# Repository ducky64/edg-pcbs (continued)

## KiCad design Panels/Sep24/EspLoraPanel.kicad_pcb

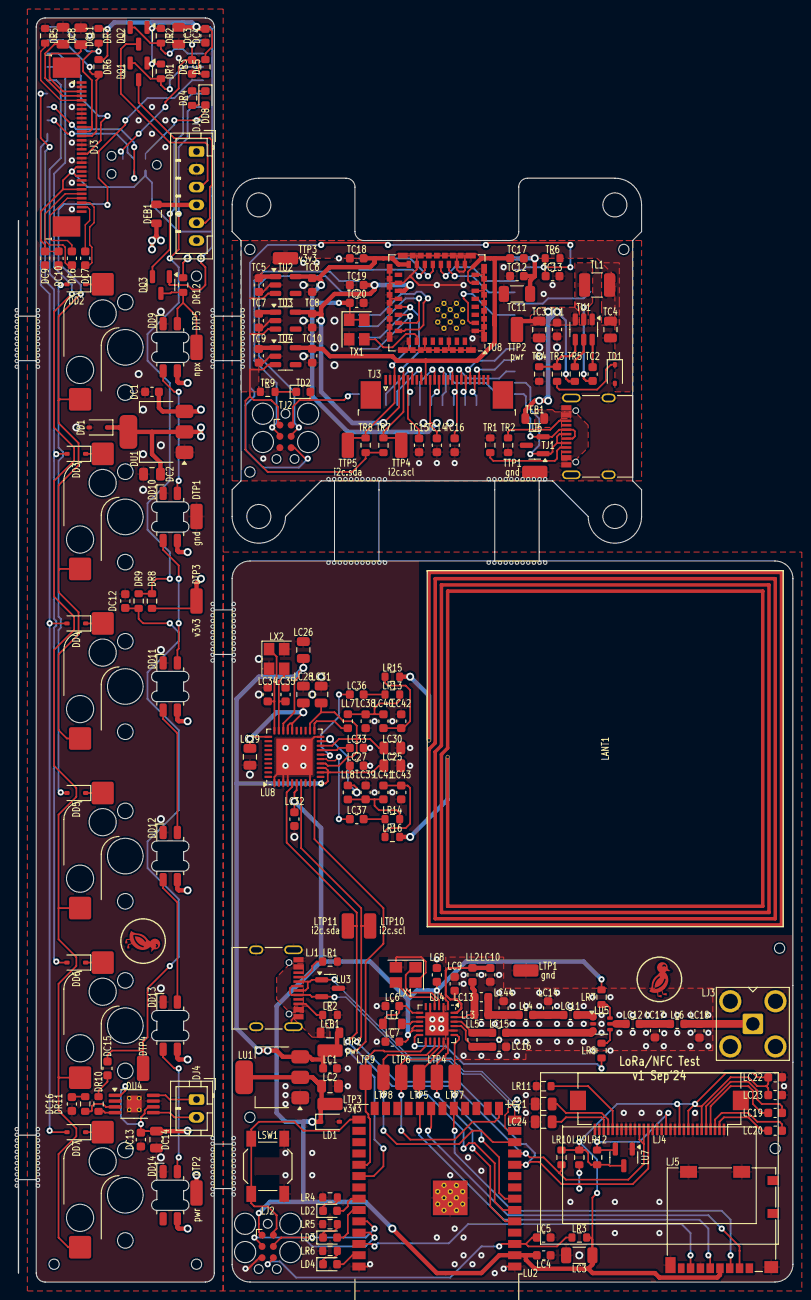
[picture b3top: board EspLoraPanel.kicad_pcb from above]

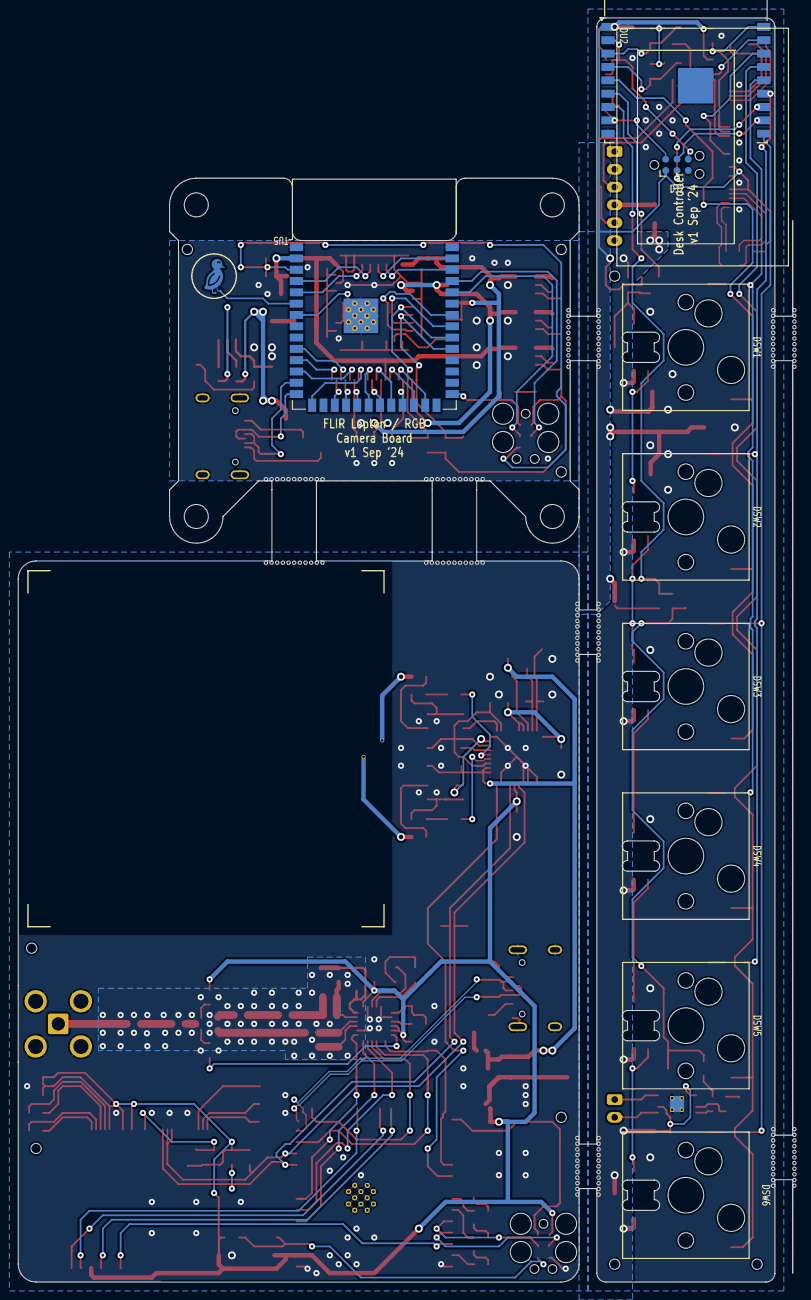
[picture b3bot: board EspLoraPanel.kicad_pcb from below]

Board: 2 copper layers, 87.0 x 142.0 mm, 227 parts (20 on the bottom side), 167 nets.

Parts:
DC1, DC4, DC13: 50V 100nF X7R ±10% 0603 Multilayer Ceramic Capaci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; C_0603_1608Metric
DC2, DC8: 25V 4.7uF X5R ±10% 0805 Multilayer Ceramic Capaci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; C_0805_2012Metric
DC3, DC11, DC14: 25V 10uF X5R ±10% 0805 Multilayer Ceramic Capacit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; C_0805_2012Metric
DC5, DC6, DC7, DC9, DC10, DC15, DC16: 50V 1uF X5R ±10% 0603 Multilayer Ceramic Capacito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; C_0603_1608Metric
DC12: 50V 33nF X7R ±10% 0603 Multilayer Ceramic Capacit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; C_0603_1608Metric
DD1: 3.6V~3.8V 200mW 3.6V SOD-323 Zener Diodes ROHS; D_SOD-323
DD2, DD3, DD4, DD5, DD6, DD7: 40V 600mV@1A 1A SOD-323 Schottky Diodes ROHS; D_SOD-323
DD8: -40?~+85? Red 0603 LED Indication - Discrete ROHS; LED_0603_1608Metric
DD9, DD10, DD11, DD12, DD13, DD14: SK6812MINI-E; LED_SK6812MINI-E
DFB1: ±25% 100?@100MHz 0805 Ferrite Beads ROHS; L_0805_2012Metric
DH1, DH2, DH3: JlcToolingHole_1.152mm
DJ1: B6B-PH-K; JST_PH_B6B-PH-K_1x06_P2.00mm_Vertical
DJ2: Tag-Connect_TC2030-IDC-NL_2x03_P1.27mm_Vertical
DJ3: AFC07-S30ECA-00; TE_3-1734839-0_1x30-1MP_P0.5mm_Horizontal
DJ4: B2B-PH-K; JST_PH_B2B-PH-K_1x02_P2.00mm_Vertical
DQ1, DQ2, DQ3: 30V 5.7A 26.5m?@10V,5.7A 1.4W 1.5V@250uA 1PCSNCha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; SOT-23
DR1, DR2, DR6, DR7, DR8, DR12: 100mW Thick Film Resistors 75V ±100ppm/? ±1% 4.7k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; R_0603_1608Metric
DR3: 100mW Thick Film Resistors 75V ±100ppm/? ±1% 10k?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; R_0603_1608Metric
DR4: 100mW Thick Film Resistors 75V ±100ppm/? ±1% 820?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; R_0603_1608Metric
DR5: 100mW Thick Film Resistors 75V ±100ppm/? ±1% 470k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; R_0603_1608Metric
DR9: 100mW Thick Film Resistors 75V ±100ppm/? ±1% 1k? 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; R_0603_1608Metric
DR10, DR11: 100mW Thick Film Resistors 75V ±100ppm/? ±1% 68k?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; R_0603_1608Metric
DSW1, DSW2, DSW3, DSW4, DSW5, DSW6: PG151101S11; SW_Hotswap_Kailh_MX
DTP1: gnd; TestPoint_TE_RCT_0805
DTP2: pwr; TestPoint_TE_RCT_0805
DTP3: v3v3; TestPoint_TE_RCT_0805
DTP4: spk_chain_1; TestPoint_TE_RCT_0805
DTP5: npx; TestPoint_TE_RCT_0805
DU1: LDL1117S33R; SOT-223-3_TabPin2
DU2: ESP32-C3-WROOM-02; ESP-WROOM-02
DU3: ER-OLED-0.96-1.1; Lcd_Er_Oled0.96_1.1_Outline
DU4: TPA2005D1; MSOP-8-1EP_3x3mm_P0.65mm_EP1.68x1.88mm_ThermalVias
LANT1: an13219
LC1, LC4, LC7, LC27, LC33: 50V 100nF X7R ±10% 0603 Multilayer Ceramic Capaci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; C_0603_1608Metric
LC2, LC21, LC25, LC26: 25V 4.7uF X5R ±10% 0805 Multilayer Ceramic Capaci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; C_0805_2012Metric
LC3: 25V 22uF X5R ±10% 1206 Multilayer Ceramic Capacit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; C_1206_3216Metric
LC5, LC8, LC19, LC20, LC22, LC23, LC32: 50V 1uF X5R ±10% 0603 Multilayer Ceramic Capacito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; C_0603_1608Metric
LC6: 25V 470nF X7R ±10% 0603 Multilayer Ceramic Capaci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; C_0603_1608Metric
LC9, LC11, LC12, LC42, LC43: 50V 47pF C0G ±5% 0603 Multilayer Ceramic Capacito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; C_0603_1608Metric
LC10: 50V 47nF X7R ±10% 0603 Multilayer Ceramic Capacit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; C_0603_1608Metric
LC13: 250V 2.2pF NP0 ±5% 0603 Multilayer Ceramic Capaci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; C_0603_1608Metric
LC14, LC15, LC16, LC17, LC18: 250V 3pF C0G ±5% 0603 Multilayer Ceramic Capacito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; C_0603_1608Metric
LC24: 25V 10uF X5R ±10% 0805 Multilayer Ceramic Capacit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; C_0805_2012Metric
LC28, LC29, LC30, LC31: 50V 2.2uF X5R ±10% 0805 Multilayer Ceramic Capaci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; C_0805_2012Metric
LC34, LC35, LC44: 50V 10pF C0G ±5% 0603 Multilayer Ceramic Capacito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; C_0603_1608Metric
LC36, LC37: 50V 1nF X7R ±10% 0603 Multilayer Ceramic Capacito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; C_0603_1608Metric
LC38, LC39: 50V 560pF X7R ±10% 0603 Multilayer Ceramic Capaci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; C_0603_1608Metric
LC40, LC41: 50V 150pF X7R ±10% 0603 Multilayer Ceramic Capaci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; C_0603_1608Metric
LD1: 3.6V~3.8V 200mW 3.6V SOD-323 Zener Diodes ROHS; D_SOD-323
LD2: -40?~+85? Red 0603 LED Indication - Discrete ROHS; LED_0603_1608Metric
LD3: 20mA Colorless transparent lens -40?~+85? 585.5nm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; LED_0603_1608Metric
LD4: White 0603 LED Indication - Discrete ROHS; LED_0603_1608Metric
LFB1: ±25% 100?@100MHz 0805 Ferrite Beads ROHS; L_0805_2012Metric
LH1, LH2, LH3: JlcToolingHole_1.152mm
LJ1: COM-15111; USB_C_Receptacle_XKB_U262-16XN-4BVC11
LJ2: Tag-Connect_TC2030-IDC-FP_2x03_P1.27mm_Vertical
LJ3: 901-143; SMA_Amphenol_901-143_Horizontal
LJ4: AFC01-S30FCA-00; Hirose_FH12-30S-0.5SH_1x30-1MP_P0.50mm_Horizontal
LJ5: 104031-0811; microSD_HC_Molex_104031-0811
LL1: 100mA 15uH ±20% 650m? 0805 Inductors (SMD) ROHS; L_0805_2012Metric
LL2: 200mA 47nH ±5% 1? 0603 Inductors (SMD) ROHS; L_0603_1608Metric
LL3: 700mA 3.3nH ±5% 0603 Power Inductors ROHS; L_0603_1608Metric
LL4, LL6: 500mA 8.2nH ±5% 350m? 0603 Inductors (SMD) ROHS; L_0603_1608Metric
LL5: 300mA 12nH ±5% 450m? 0603 Inductors (SMD) ROHS; L_0603_1608Metric
LL7, LL8: 900mA 220nH ±5% 200m? 0603 Inductors (SMD) ROHS; L_0603_1608Metric
LR1, LR2: 100mW Thick Film Resistors 75V ±100ppm/? ±1% 5.1k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; R_0603_1608Metric
LR3, LR12: 100mW Thick Film Resistors 75V ±100ppm/? ±1% 10k?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; R_0603_1608Metric
LR4, LR5, LR6: 100mW Thick Film Resistors 75V ±100ppm/? ±1% 820?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; R_0603_1608Metric
LR7, LR8: 100mW Thick Film Resistors 75V ±100ppm/? ±1% 1k? 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; R_0603_1608Metric
LR9, LR10: 100mW Thick Film Resistors 75V ±100ppm/? ±1% 4.7k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; R_0603_1608Metric
LR11: 100mW Thick Film Resistors 75V ±100ppm/? ±1% 470k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; R_0603_1608Metric
LR13, LR14: 100mW Thick Film Resistors 75V ±100ppm/? ±1% 2.2k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; R_0603_1608Metric
LR15, LR16: 100mW Thick Film Resistors 75V ±1% ±200ppm/? 2.49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; R_0603_1608Metric
LSW1: 5.1mm switch; SW_SPST_SKQG_WithoutStem
LTP1: gnd; TestPoint_TE_RCT_0805
LTP2: pwr; TestPoint_TE_RCT_0805
LTP3: v3v3; TestPoint_TE_RCT_0805
LTP4: lr.sck; TestPoint_TE_RCT_0805
LTP5: lr.mosi; TestPoint_TE_RCT_0805
LTP6: lr.miso; TestPoint_TE_RCT_0805
LTP7: lr_cs; TestPoint_TE_RCT_0805
LTP8: lr_rs; TestPoint_TE_RCT_0805
LTP9: lr_di; TestPoint_TE_RCT_0805
LTP10: i2c.scl; TestPoint_TE_RCT_0805
LTP11: i2c.sda; TestPoint_TE_RCT_0805
LU1: LDL1117S33R; SOT-223-3_TabPin2
LU2: ESP32-S3-WROOM-1-N16R8; ESP32-S3-WROOM-1
LU3: PESD5V0X1BT; SOT-23
LU4: SX1262IMLTRT; QFN-24-1EP_4x4mm_P0.5mm_EP2.6x2.6mm
LU5: PE4259; SOT-363_SC-70-6
LU6: ER-OLED-0.96-1.1; Lcd_Er_Oled0.96_1.1_Outline
LU7: APX803S-29SA-7; SOT-23
LU8: PN7160A1HN/C100Y; HVQFN-40-1EP_6x6mm_P0.5mm_EP4.1x4.1mm
LX1: 30MHz SMD Crystal Resonator 20pF ±10ppm ±30ppm -4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; Crystal_SMD_3225-4Pin_3.2x2.5mm
LX2: 27.12MHz SMD Crystal Resonator 10pF ±10ppm ±30ppm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; Crystal_SMD_3225-4Pin_3.2x2.5mm
TC1, TC2, TC12, TC14, TC15, TC17, TC18, TC19, TC20: 50V 100nF X7R ±10% 0603 Multilayer Ceramic Capaci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; C_0603_1608Metric
TC3, TC4: 25V 10uF X5R ±10% 0805 Multilayer Ceramic Capacit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; C_0805_2012Metric
TC5, TC6, TC7, TC8, TC9, TC10, TC13: 50V 1uF X5R ±10% 0603 Multilayer Ceramic Capacito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; C_0603_1608Metric
TC11: 25V 22uF X5R ±10% 1206 Multilayer Ceramic Capacit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; C_1206_3216Metric
TC16: 50V 15pF C0G ±5% 0603 Multilayer Ceramic Capacito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; C_0603_1608Metric
TD1: 3.6V~3.8V 200mW 3.6V SOD-323 Zener Diodes ROHS; D_SOD-323
TD2: -40?~+85? Red 0603 LED Indication - Discrete ROHS; LED_0603_1608Metric
TFB1: ±25% 100?@100MHz 0805 Ferrite Beads ROHS; L_0805_2012Metric
TH1, TH2, TH3: JlcToolingHole_1.152mm
TJ1: COM-15111; USB_C_Receptacle_XKB_U262-16XN-4BVC11
TJ2: Tag-Connect_TC2030-IDC-FP_2x03_P1.27mm_Vertical
TJ3: AFC07-S24ECA-00; TE_2-1734839-4_1x24-1MP_P0.5mm_Horizontal
TL1: 1.2A 10uH ±20% 1.6A 305m? 1210 Inductors (SMD) RO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; L_1210_3225Metric
TR1, TR2: 100mW Thick Film Resistors 75V ±100ppm/? ±1% 5.1k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; R_0603_1608Metric
TR3: 100mW Thick Film Resistors 75V ±100ppm/? ±1% 6.8k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; R_0603_1608Metric
TR4: 100mW Thick Film Resistors 75V ±100ppm/? ±1% 1.5k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; R_0603_1608Metric
TR5: 100mW Thick Film Resistors 75V ±100ppm/? ±1% 510k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; R_0603_1608Metric
TR6: 100mW Thick Film Resistors 75V ±100ppm/? ±1% 10k?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; R_0603_1608Metric
TR7, TR8: 100mW Thick Film Resistors 75V ±100ppm/? ±1% 4.7k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; R_0603_1608Metric
TR9: 100mW Thick Film Resistors 75V ±100ppm/? ±1% 820?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; R_0603_1608Metric
TTP1: gnd; TestPoint_TE_RCT_0805
TTP2: pwr; TestPoint_TE_RCT_0805
TTP3: v3v3; TestPoint_TE_RCT_0805
TTP4: i2c.scl; TestPoint_TE_RCT_0805
TTP5: i2c.sda; TestPoint_TE_RCT_0805
TU1: TPS54202H; SOT-23-6
TU2: TLV75730PDBVR; SOT-23-5
TU3: TLV75728PDBVR; SOT-23-5
TU4: TLV75712PDBVR; SOT-23-5
TU5: ESP32-S3-WROOM-1-N16R8; ESP32-S3-WROOM-1
TU6: PESD5V0X1BT; SOT-23
TU7: Symbol_DucklingSolid
TU8: 1050281001; Molex_1050281001
TX1: ±15ppm 1.8V~3.3V 25MHz -40?~+85? SMD-3225_4P Pre-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; Crystal_SMD_3225-4Pin_3.2x2.5mm
svg2mod, svg2mod#2: G***; Symbol_DucklingSolid

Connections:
Dconn.dtx_shift.hv_io: DJ1.5, DQ1.3
Dconn.htx_shift.hv_io: DJ1.3, DQ2.3
Dconn.pwr: DFB1.1, DJ1.4
Dconn.uart.rx: DQ2.2, DR2.2, DU2.3
Dconn.uart.tx: DQ1.2, DR1.2, DU2.4
Dgnd: DC1.2, DC2.2, DC3.2, DC4.2, DC5.2, DC8.2, DC9.2, DC10.2, DC11.2, DC12.2, DC13.2, DC14.2, DC16.2, DD1.2, DD9.3, DD10.3, DD11.3, DD12.3, DD13.3, DD14.3, DJ1.2, DJ2.5, DJ3.1, DJ3.2, DJ3.6, DJ3.7, DJ3.8, DJ3.9, DJ3.10, DJ3.14, DJ3.15, DJ3.16, DJ3.18, DJ3.19, DJ3.21, DJ3.23, DJ3.30, DR4.2, DR5.2, DTP1.1, DU1.1, DU2.9, DU2.19, DU4.7, DU4.9
Di2c_pull.i2c.scl: DJ3.13, DR6.2, DU2.17
Di2c_pull.i2c.sda: DJ3.11, DJ3.12, DR7.2, DU2.18
Dledr.res.a: DD8.1, DR4.1
Dmcu.gpio.swc_0: DSW1.2, DSW2.2, DSW3.2, DU2.5
Dmcu.gpio.swc_1: DSW4.2, DSW5.2, DSW6.2, DU2.15
Dmcu.gpio.swr_0: DD2.2, DD5.2, DU2.14
Dmcu.gpio.swr_1: DD3.2, DD6.2, DU2.13
Dmcu.gpio.swr_2: DD4.2, DD7.2, DU2.10
Dmcu.program_boot_node: DD8.2, DJ2.2, DU2.8
Dmcu.program_en_node: DC5.1, DJ2.6, DR3.2, DU2.2
Dmcu.program_uart_node.a_tx: DJ2.3, DU2.12
Dmcu.program_uart_node.b_tx: DJ2.4, DU2.11
Dnpx.led[0].dout: DD9.2, DD10.4
Dnpx.led[1].dout: DD10.2, DD11.4
Dnpx.led[2].dout: DD11.2, DD12.4
Dnpx.led[3].dout: DD12.2, DD13.4
Dnpx.led[4].dout: DD13.2, DD14.4
Dnpx_shift.hv_io: DD9.4, DQ3.3, DR12.2, DTP5.1
Dnpx_shift.lv_io: DQ3.2, DU2.6
Doled.c1_cap.neg: DC6.2, DJ3.26
Doled.c1_cap.pos: DC6.1, DJ3.27
Doled.c2_cap.neg: DC7.2, DJ3.28
Doled.c2_cap.pos: DC7.1, DJ3.29
Doled.device.vcc: DC11.1, DJ3.3
Doled.device.vcomh: DC8.1, DJ3.4
Doled.iref_res.a: DJ3.5, DR5.1
Doled.reset: DJ3.17, DU2.16
Dpwr: DC1.1, DC13.1, DC14.1, DD9.1, DD10.1, DD11.1, DD12.1, DD13.1, DD14.1, DFB1.2, DR12.1, DTP2.1, DU1.3, DU4.1, DU4.6
Dspk_chain_0: DR8.2, DR9.1, DU2.7
Dspk_chain_1: DC12.1, DC15.2, DR9.2, DTP4.1
Dspk_chain_2.a: DJ4.1, DU4.8
Dspk_chain_2.b: DJ4.2, DU4.5
Dspk_drv.inn_cap.pos: DC16.1, DR11.1
Dspk_drv.inn_res.b: DR11.2, DU4.3
Dspk_drv.inp_cap.pos: DC15.1, DR10.1
Dspk_drv.inp_res.b: DR10.2, DU4.4
Dsw.d[0,0].cathode: DD2.1, DSW1.1
Dsw.d[0,1].cathode: DD3.1, DSW2.1
Dsw.d[0,2].cathode: DD4.1, DSW3.1
Dsw.d[1,0].cathode: DD5.1, DSW4.1
Dsw.d[1,1].cathode: DD6.1, DSW5.1
Dsw.d[1,2].cathode: DD7.1, DSW6.1
Dv3v3: DC2.1, DC3.1, DC4.1, DC9.1, DC10.1, DD1.1, DJ2.1, DJ3.20, DJ3.22, DJ3.25, DQ1.1, DQ2.1, DQ3.1, DR1.1, DR2.1, DR3.1, DR6.1, DR7.1, DR8.1, DTP3.1, DU1.2, DU2.1
Lgnd: LC1.2, LC2.2, LC3.2, LC4.2, LC5.2, LC6.2, LC7.2, LC8.2, LC9.2, LC10.2, LC14.2, LC16.2, LC17.2, LC18.2, LC21.2, LC22.2, LC23.2, LC24.2, LC25.2, LC26.2, LC27.2, LC28.2, LC29.2, LC30.2, LC31.2, LC32.2, LC33.2, LC34.2, LC35.2, LC38.2, LC39.2, LC42.2, LC43.2, LC44.2, LD1.2, LJ1.A1, LJ1.A12, LJ1.B1, LJ1.B12, LJ1.S1, LJ2.5, LJ3.2, LJ4.1, LJ4.8, LJ4.10, LJ4.12, LJ4.13, LJ4.15, LJ4.16, LJ4.17, LJ4.21, LJ4.22, LJ4.23, LJ4.24, LJ4.25, LJ4.29, LJ4.30, LJ5.6, LJ5.11, LR1.1, LR2.1, LR4.2, LR5.2, LR6.2, LR11.2, LSW1.2, LTP1.1, LU1.1, LU2.1, LU2.40, LU2.41, LU3.3, LU4.2, LU4.5, LU4.8, LU4.20, LU4.25, LU5.2, LU7.1, LU8.1, LU8.3, LU8.4, LU8.9, LU8.20, LU8.41, LX1.2, LX1.4, LX2.2, LX2.4
Li2c_pull.i2c.scl: LJ4.18, LR9.2, LTP10.1, LU2.10, LU8.7
Li2c_pull.i2c.sda: LJ4.19, LJ4.20, LR10.2, LTP11.1, LU2.11, LU8.5
Lledb.res.a: LD4.1, LR6.1
Lledb.signal: LD4.2, LU2.39
Lledg.res.a: LD3.1, LR5.1
Lledg.signal: LD3.2, LU2.35
Lledr.res.a: LD2.1, LR4.1
Lledr.signal: LD2.2, LU2.34
Llora.ant_pi.output: LC18.1, LJ3.1, LL6.2
Llora.balun.input: LC15.1, LU5.3
Llora.balun.rfi_n: LC15.2, LL5.1, LU4.22
Llora.balun.rfi_p: LC16.1, LL5.2, LU4.21
Llora.dcc_l.a: LL1.1, LU4.9
Llora.ic.rfo: LC13.2, LL2.2, LL3.1, LU4.23
Llora.ic.vr_pa: LC9.1, LC10.1, LL2.1, LU4.24
Llora.ic.vreg: LC6.1, LL1.2, LU4.7
Llora.rf_sw.ctrl: LR8.1, LU4.12
Llora.rf_sw.ctrl_res.b: LR8.2, LU5.4
Llora.rf_sw.vdd_res.b: LR7.2, LU5.6
Llora.rfc_dcblock.neg: LC12.2, LU5.5
Llora.rfc_dcblock.pos: LC12.1, LC17.1, LL6.1
Llora.tx_dcblock.pos: LC11.1, LU5.1
Llora.tx_pi.output: LC11.2, LC14.1, LL4.2
Llora.xtal.crystal.xtal_in: LU4.3, LX1.1
Llora.xtal.crystal.xtal_out: LU4.4, LX1.3
Lmcu.program_boot_node: LJ2.2, LSW1.1, LU2.27
Lmcu.program_en_node: LC5.1, LJ2.6, LR3.2, LU2.3
Lmcu.program_uart_node.a_tx: LJ2.3, LU2.37
Lmcu.program_uart_node.b_tx: LJ2.4, LU2.36
Lnfc.damp.ant1: LANT1.1, LR15.2
Lnfc.damp.ant2: LANT1.2, LR16.2
Lnfc.emc.out1: LC38.1, LC40.1, LL7.2, LR13.1
Lnfc.emc.out2: LC39.1, LC41.1, LL8.2, LR14.1
Lnfc.ic.rxn: LC37.2, LU8.15
Lnfc.ic.rxp: LC36.2, LU8.16
Lnfc.ic.tx1: LL7.1, LU8.21
Lnfc.ic.tx2: LL8.1, LU8.19
Lnfc.ic.vdd: LC28.1, LC29.1, LU8.26, LU8.27, LU8.31
Lnfc.ic.vddmid: LC33.1, LU8.17
Lnfc.ic.vddtx: LC30.1, LC31.1, LU8.14, LU8.18, LU8.22
Lnfc.ic.xtal.xtal_in: LC34.1, LU8.30, LX2.1
Lnfc.ic.xtal.xtal_out: LC35.1, LU8.29, LX2.3
Lnfc.match.out1: LC40.2, LC42.1, LR15.1
Lnfc.match.out2: LC41.2, LC43.1, LR16.1
Lnfc.reset: LU2.32, LU8.10
Lnfc.rx.rrx1.b: LC36.1, LR13.2
Lnfc.rx.rrx2.b: LC37.1, LR14.2
Loled.c1_cap.neg: LC19.2, LJ4.5
Loled.c1_cap.pos: LC19.1, LJ4.4
Loled.c2_cap.neg: LC20.2, LJ4.3
Loled.c2_cap.pos: LC20.1, LJ4.2
Loled.device.vcc: LC24.1, LJ4.28
Loled.device.vcomh: LC21.1, LJ4.27
Loled.iref_res.a: LJ4.26, LR11.1
Loled_rst.nreset: LJ4.14, LR12.2, LU7.2
Lpwr: LC1.1, LC25.1, LC26.1, LC27.1, LFB1.2, LTP2.1, LU1.3, LU8.12, LU8.13, LU8.28
Lsd.cs: LJ5.2, LU2.21
Lsd.spi.miso: LJ5.7, LU2.38
Lsd.spi.mosi: LJ5.3, LU2.19
Lsd.spi.sck: LJ5.5, LU2.22
Ltp_lora_cs.io: LTP7.1, LU2.7, LU4.19
Ltp_lora_dio.io: LTP9.1, LU2.31, LU4.13
Ltp_lora_rst.io: LTP8.1, LU2.12, LU4.15
Ltp_lora_spi.io.miso: LTP6.1, LU2.15, LU4.16
Ltp_lora_spi.io.mosi: LTP5.1, LU2.6, LU4.17
Ltp_lora_spi.io.sck: LTP4.1, LU2.5, LU4.18
Ltx_cpack.pos.0: LC13.1, LC44.1, LL3.2, LL4.1
Lusb.conn.cc.cc1: LJ1.A5, LR1.2
Lusb.conn.cc.cc2: LJ1.B5, LR2.2
Lusb.pwr: LFB1.1, LJ1.A4, LJ1.A9, LJ1.B4, LJ1.B9
Lusb_chain_0.d_N: LJ1.A7, LJ1.B7, LU2.13, LU3.1
Lusb_chain_0.d_P: LJ1.A6, LJ1.B6, LU2.14, LU3.2
Lv3v3: LC2.1, LC3.1, LC4.1, LC7.1, LC8.1, LC22.1, LC23.1, LC32.1, LD1.1, LJ2.1, LJ4.6, LJ4.9, LJ4.11, LJ5.4, LR3.1, LR7.1, LR9.1, LR10.1, LR12.1, LTP3.1, LU1.2, LU2.2, LU4.1, LU4.10, LU4.11, LU7.3, LU8.6
Tcam.dvp8.href: TJ3.9, TU5.24
Tcam.dvp8.pclk: TC16.1, TJ3.17, TU5.19
Tcam.dvp8.vsync: TJ3.7, TU5.25
Tcam.dvp8.xclk: TJ3.13, TU5.21
Tcam.dvp8.y0: TJ3.19, TU5.18
Tcam.dvp8.y1: TJ3.21, TU5.17
Tcam.dvp8.y2: TJ3.22, TU5.11
Tcam.dvp8.y3: TJ3.20, TU5.10
Tcam.dvp8.y4: TJ3.18, TU5.12
Tcam.dvp8.y5: TJ3.16, TU5.15
Tcam.dvp8.y6: TJ3.14, TU5.20
Tcam.dvp8.y7: TJ3.12, TU5.22
Tcam.reset: TC15.1, TJ3.6, TU5.23
Tflir.cs: TU5.38, TU8.14
Tflir.mclk.out: TU8.26, TX1.3
Tflir.reset: TU5.34, TU8.24
Tflir.shutdown: TU5.33, TU8.23
Tflir.spi.miso: TU5.4, TU8.12
Tflir.spi.mosi: TU5.5, TU8.11
Tflir.spi.sck: TU5.39, TU8.13
Tflir.vsync: TU5.7, TU8.2
Tgnd: TC1.2, TC3.2, TC4.2, TC5.2, TC6.2, TC7.2, TC8.2, TC9.2, TC10.2, TC11.2, TC12.2, TC13.2, TC14.2, TC15.2, TC16.2, TC17.2, TC18.2, TC19.2, TC20.2, TD1.2, TJ1.A1, TJ1.A12, TJ1.B1, TJ1.B12, TJ1.S1, TJ2.5, TJ3.2, TJ3.8, TJ3.15, TR1.1, TR2.1, TR4.2, TR9.2, TTP1.1, TU1.1, TU2.2, TU3.2, TU4.2, TU5.1, TU5.40, TU5.41, TU6.3, TU8.1, TU8.6, TU8.8, TU8.9, TU8.10, TU8.15, TU8.18, TU8.20, TU8.25, TU8.27, TU8.30, TU8.33, TX1.2
Ti2c_chain_0.scl: TJ3.5, TR7.2, TTP4.1, TU5.32, TU8.21
Ti2c_chain_0.sda: TJ3.3, TR8.2, TTP5.1, TU5.31, TU8.22
Tledr.res.a: TD2.1, TR9.1
Tmcu.program_boot_node: TD2.2, TJ2.2, TU5.27
Tmcu.program_en_node: TC13.1, TJ2.6, TR6.2, TU5.3
Tmcu.program_uart_node.a_tx: TJ2.3, TU5.37
Tmcu.program_uart_node.b_tx: TJ2.4, TU5.36
Tpwr: TC1.1, TC3.1, TFB1.2, TR5.1, TTP2.1, TU1.3
Treg_3v3.boot_cap.neg: TC2.2, TL1.1, TU1.2
Treg_3v3.boot_cap.pos: TC2.1, TU1.6
Treg_3v3.en_res.b: TR5.2, TU1.5
Treg_3v3.fb.output: TR3.2, TR4.1, TU1.4
Ttouch_duck.pad: TU5.6, TU7.1
Tusb.conn.cc.cc1: TJ1.A5, TR1.2
Tusb.conn.cc.cc2: TJ1.B5, TR2.2
Tusb.pwr: TFB1.1, TJ1.A4, TJ1.A9, TJ1.B4, TJ1.B9
Tusb_chain_0.d_N: TJ1.A7, TJ1.B7, TU5.13, TU6.1
Tusb_chain_0.d_P: TJ1.A6, TJ1.B6, TU5.14, TU6.2
Tv1v2: TC10.1, TC17.1, TJ3.10, TU4.5, TU8.7
Tv2v8: TC8.1, TC19.1, TJ3.4, TU3.5, TU8.19
Tv3v0: TC6.1, TC14.1, TC18.1, TC20.1, TJ3.11, TU2.5, TU8.16, TX1.1, TX1.4
Tv3v3: TC4.1, TC5.1, TC7.1, TC9.1, TC11.1, TC12.1, TD1.1, TJ2.1, TL1.2, TR3.1, TR6.1, TR7.1, TR8.1, TTP3.1, TU2.1, TU2.3, TU3.1, TU3.3, TU4.1, TU4.3, TU5.2

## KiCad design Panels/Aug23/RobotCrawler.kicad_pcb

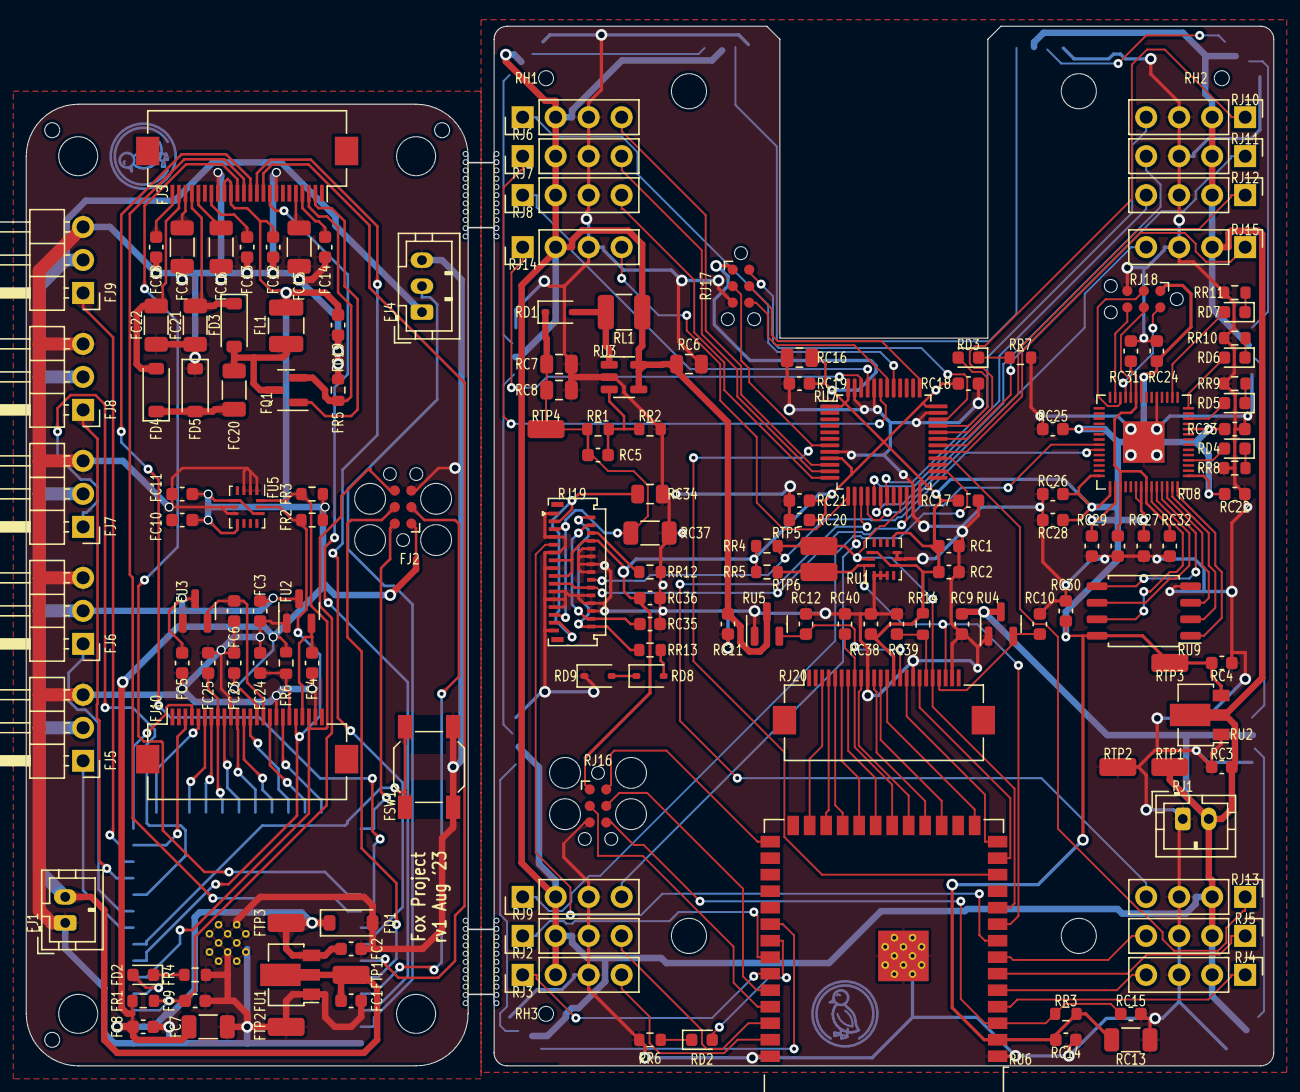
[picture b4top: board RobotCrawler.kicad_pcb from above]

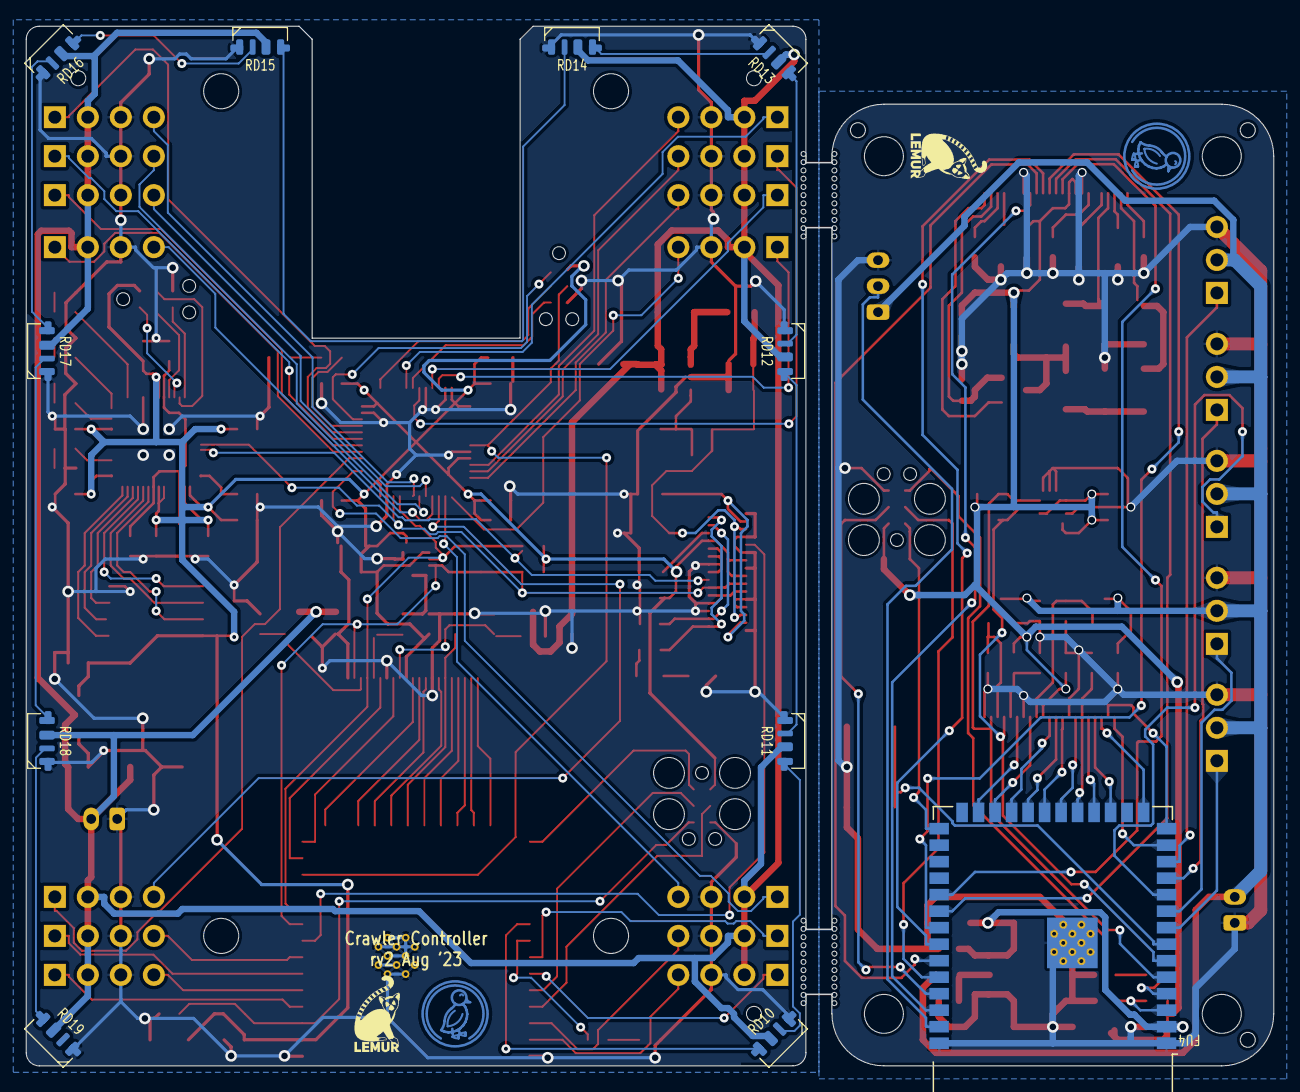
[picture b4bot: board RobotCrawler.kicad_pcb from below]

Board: 2 copper layers, 96.0 x 80.0 mm, 184 parts (15 on the bottom side), 150 nets.

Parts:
FC1, FC2, FC3, FC4, FC5, FC6, FC8, FC9, FC10, FC11, FC12, FC13, FC14, FC18, FC19, FC23, FC24, FC25: C_0603_1608Metric
FC7, FC15, FC16, FC17, FC20, FC21, FC22: C_1206_3216Metric
FD1: BZT52C3V6 (SMC(Sangdest Microelectronicstronic (N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; D_SOD-123
FD2: LED_0603_1608Metric
FD3, FD4, FD5: B5817W (Guangdong Hottech) - 20V 450mV@1A 300mA S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; D_SOD-123
FH1, FH2, FH3: JlcToolingHole_1.152mm
FJ1: B2B-PH-K (JST); JST_PH_B2B-PH-K_1x02_P2.00mm_Vertical
FJ2: Tag-Connect_TC2030-IDC-FP_2x03_P1.27mm_Vertical
FJ3, FJ10: AFC01-S24FCA-00 (Jushuo); Hirose_FH12-24S-0.5SH_1x24-1MP_P0.50mm_Horizontal
FJ4: B3B-PH-K (JST); JST_PH_B3B-PH-K_1x03_P2.00mm_Vertical
FJ5, FJ6, FJ7, FJ8, FJ9: PinHeader2.54 1x3 Horizontal (Generic); PinHeader_1x03_P2.54mm_Horizontal
FL1: L_1210_3225Metric
FQ1: AO3400A (Alpha & Omega Semicon) - 30V 5.7A 26.5m?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; SOT-23
FR1, FR2, FR3, FR4, FR5, FR6: R_0603_1608Metric
FSW1: 5.1mm switch; SW_SPST_SKQG_WithoutStem
FTP1: 5015 (Keystone) - pwr; TestPoint_TE_RCT_0805
FTP2: 5015 (Keystone) - gnd; TestPoint_TE_RCT_0805
FTP3: 5015 (Keystone) - v3v3; TestPoint_TE_RCT_0805
FU1: AP7215-33YG-13 (Diodes Incorporated); SOT-89-3
FU2: XC6206P252MR (Torex Semiconductor Ltd); SOT-23
FU3: XC6206P122MR-G (Torex Semiconductor Ltd); SOT-23
FU4: ESP32-S3-WROOM-1-N16R8 (Espressif Systems); ESP32-S3-WROOM-1
FU5: LSM6DS3TR-C (STMicroelectronics); Bosch_LGA-14_3x2.5mm_P0.5mm
H10, H11#2, H12, H13: MountingHole_3mm
H10#2, H11, H12#2, H14: MountingHole_2.7mm_M2.5
RC1, RC2, RC3, RC4, RC5, RC9, RC10, RC11, RC12, RC14, RC15, RC17, RC18, RC19, RC20, RC21, RC22, RC23, RC24, RC25, RC26, RC27, RC28, RC29, RC30, RC31, RC32, RC33, RC35, RC36, RC38, RC39, RC40: C_0603_1608Metric
RC6, RC7, RC8, RC16, RC34: C_0805_2012Metric
RC13, RC37: C_1206_3216Metric
RD1: CUS10S30,H3F (TOSHIBA) - 30V 230mV@100mA 1A SOD-3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; D_SOD-323
RD2, RD3, RD4, RD5, RD6, RD7: LED_0603_1608Metric
RD8, RD9: 1N5819WS (Guangdong Hottech) - 40V 600mV@1A 1A SO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; D_SOD-323
RD10, RD11, RD12, RD13, RD14, RD15, RD16, RD17, RD18, RD19: SK6812 SIDE-A (Normand Electronic Co Ltd); LED_SK6812-SIDE-A
RH1, RH2, RH3: JlcToolingHole_1.152mm
RJ1: B2B-PH-K (JST); JST_PH_B2B-PH-K_1x02_P2.00mm_Vertical
RJ2, RJ3, RJ4, RJ5, RJ6, RJ7, RJ8, RJ9, RJ10, RJ11, RJ12, RJ13, RJ14, RJ15: PinHeader2.54 1x4 (Generic); PinHeader_1x04_P2.54mm_Vertical
RJ16: Tag-Connect_TC2030-IDC-FP_2x03_P1.27mm_Vertical
RJ17, RJ18: Tag-Connect_TC2030-IDC-NL_2x03_P1.27mm_Vertical
RJ19: FH35C-31S-0.3SHW (Hirose); Hirose_FH35C-31S-0.3SHW_1x31-1MP_P0.30mm_Horizontal
RJ20: AFC01-S24FCA-00 (Jushuo); Hirose_FH12-24S-0.5SH_1x24-1MP_P0.50mm_Horizontal
RL1: L_1210_3225Metric
RR1, RR2, RR3, RR4, RR5, RR6, RR7, RR8, RR9, RR10, RR11, RR12, RR13, RR14: R_0603_1608Metric
RTP1: 5015 (Keystone) - vbatt; TestPoint_TE_RCT_0805
RTP2: 5015 (Keystone) - gnd; TestPoint_TE_RCT_0805
RTP3: 5015 (Keystone) - v3v3; TestPoint_TE_RCT_0805
RTP4: 5015 (Keystone) - v14; TestPoint_TE_RCT_0805
RTP5: 5015 (Keystone) - i2c_chain_0.scl; TestPoint_TE_RCT_0805
RTP6: 5015 (Keystone) - i2c_tp._io_sda_link; TestPoint_TE_RCT_0805
RU1: LSM6DS3TR-C (STMicroelectronics); Bosch_LGA-14_3x2.5mm_P0.5mm
RU2: AP7215-33YG-13 (Diodes Incorporated); SOT-89-3
RU3: TPS61040DBVR (Texas Instruments); SOT-23-5
RU4: XC6206P252MR (Torex Semiconductor Ltd); SOT-23
RU5: XC6206P122MR-G (Torex Semiconductor Ltd); SOT-23
RU6: ESP32-S3-WROOM-1-N16R8 (Espressif Systems); ESP32-S3-WROOM-1
RU7: STM32F103xxT6 (STMicroelectronics); LQFP-48_7x7mm_P0.5mm
RU8: RP2040 (Raspberry Pi); QFN-56-1EP_7x7mm_P0.4mm_EP3.2x3.2mm
RU9: W25Q128JVSIQ (Winbond Electronics); SOIC-8_5.23x5.23mm_P1.27mm
UU4, UU4#2: Duck; Symbol_Duckling
UU5, UU5#2: Lemur; Symbol_LemurSmall

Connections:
Fcam.device.reset: FC24.1, FJ10.19, FR6.2
Fcam.dvp8.href: FJ10.16, FU4.24
Fcam.dvp8.pclk: FC25.1, FJ10.8, FU4.19
Fcam.dvp8.vsync: FJ10.18, FU4.25
Fcam.dvp8.xclk: FJ10.12, FU4.22
Fcam.dvp8.y0: FJ10.6, FU4.17
Fcam.dvp8.y1: FJ10.4, FU4.14
Fcam.dvp8.y2: FJ10.3, FU4.13
Fcam.dvp8.y3: FJ10.5, FU4.15
Fcam.dvp8.y4: FJ10.7, FU4.18
Fcam.dvp8.y5: FJ10.9, FU4.20
Fcam.dvp8.y6: FJ10.11, FU4.21
Fcam.dvp8.y7: FJ10.13, FU4.23
Fepd.boost.boot_cap.neg: FC20.2, FD4.1, FD5.2
Fepd.boost.inductor.b: FC20.1, FD3.2, FL1.2, FQ1.3
Fepd.boost.neg_out: FC22.2, FD4.2, FJ3.23
Fepd.boost.pos_out: FC21.1, FD3.1, FJ3.21
Fepd.busy: FJ3.9, FU4.38
Fepd.cs: FJ3.12, FU4.33
Fepd.dc: FJ3.11, FU4.34
Fepd.device.gdr: FJ3.2, FQ1.1
Fepd.device.rese: FJ3.3, FQ1.2, FR5.1
Fepd.device.vcom: FC18.1, FJ3.24
Fepd.device.vdd1v8: FC13.1, FJ3.18
Fepd.device.vgh: FC15.1, FJ3.5
Fepd.device.vgl: FC14.2, FJ3.4
Fepd.device.vsh: FC16.1, FJ3.20
Fepd.device.vsl: FC17.2, FJ3.22
Fepd.reset: FJ3.10, FU4.35
Fepd.spi.mosi: FJ3.14, FU4.31
Fepd.spi.sck: FJ3.13, FU4.32
Fgnd: FC1.2, FC2.2, FC3.2, FC4.2, FC5.2, FC6.2, FC7.2, FC8.2, FC9.2, FC10.2, FC11.2, FC12.2, FC13.2, FC14.1, FC15.2, FC16.2, FC17.1, FC18.2, FC19.2, FC21.2, FC22.1, FC23.2, FC24.2, FC25.2, FD1.2, FD5.1, FJ1.1, FJ2.5, FJ3.8, FJ3.17, FJ4.3, FJ5.3, FJ6.3, FJ7.3, FJ8.3, FJ9.3, FJ10.10, FJ10.17, FJ10.23, FR4.2, FR5.2, FSW1.2, FTP2.1, FU1.1, FU2.1, FU3.1, FU4.1, FU4.40, FU4.41, FU5.1, FU5.2, FU5.3, FU5.6, FU5.7
Fi2c_chain_0.scl: FJ10.20, FR2.2, FU4.6, FU5.13
Fi2c_chain_0.sda: FJ10.22, FR3.2, FU4.5, FU5.14
Fled.res.a: FD2.1, FR4.1
Fled.signal: FD2.2, FU4.4
Fmcu.program_boot_node: FJ2.2, FU4.27
Fmcu.program_en_node: FC9.1, FJ2.6, FR1.2, FU4.3
Fmcu.program_uart_node.a_tx: FJ2.3, FU4.37
Fmcu.program_uart_node.b_tx: FJ2.4, FU4.36
Fpixels.din: FJ4.2, FU4.39
Fpwr: FC1.1, FC3.1, FC5.1, FJ1.2, FJ4.1, FJ5.2, FJ6.2, FJ7.2, FJ8.2, FJ9.2, FTP1.1, FU1.2, FU2.3, FU3.3
Fservos[0].pwm: FJ5.1, FU4.8
Fservos[1].pwm: FJ6.1, FU4.9
Fservos[2].pwm: FJ7.1, FU4.10
Fservos[3].pwm: FJ8.1, FU4.11
Fservos[4].pwm: FJ9.1, FU4.12
Fsw.out: FSW1.1, FU4.7
Fv1v2: FC6.1, FJ10.15, FU3.2
Fv2v5: FC4.1, FJ10.21, FU2.2
Fv3v3: FC2.1, FC7.1, FC8.1, FC10.1, FC11.1, FC12.1, FC19.1, FC23.1, FD1.1, FJ2.1, FJ3.15, FJ3.16, FJ10.14, FL1.1, FR1.1, FR2.1, FR3.1, FR6.1, FTP3.1, FU1.3, FU4.2, FU5.5, FU5.8, FU5.12
Rcam.device.reset: RC39.1, RJ20.19, RR14.2
Rcam.dvp8.href: RJ20.16, RU6.14
Rcam.dvp8.pclk: RC40.1, RJ20.8, RU6.20
Rcam.dvp8.vsync: RJ20.18, RU6.13
Rcam.dvp8.xclk: RJ20.12, RU6.17
Rcam.dvp8.y0: RJ20.6, RU6.22
Rcam.dvp8.y1: RJ20.4, RU6.24
Rcam.dvp8.y2: RJ20.3, RU6.25
Rcam.dvp8.y3: RJ20.5, RU6.23
Rcam.dvp8.y4: RJ20.7, RU6.21
Rcam.dvp8.y5: RJ20.9, RU6.19
Rcam.dvp8.y6: RJ20.11, RU6.18
Rcam.dvp8.y7: RJ20.13, RU6.15
Rgnd: RC1.2, RC2.2, RC3.2, RC4.2, RC6.2, RC7.2, RC8.2, RC9.2, RC10.2, RC11.2, RC12.2, RC13.2, RC14.2, RC15.2, RC16.2, RC17.2, RC18.2, RC19.2, RC20.2, RC21.2, RC22.2, RC23.2, RC24.2, RC25.2, RC26.2, RC27.2, RC28.2, RC29.2, RC30.2, RC31.2, RC32.2, RC33.2, RC34.2, RC35.2, RC36.2, RC37.2, RC38.2, RC39.2, RC40.2, RD9.1, RD10.4, RD11.4, RD12.4, RD13.4, RD14.4, RD15.4, RD16.4, RD17.4, RD18.4, RD19.4, RJ1.1, RJ2.3, RJ3.3, RJ4.3, RJ5.3, RJ6.3, RJ7.3, RJ8.3, RJ9.3, RJ10.3, RJ11.3, RJ12.3, RJ13.3, RJ14.3, RJ15.3, RJ16.5, RJ17.5, RJ18.5, RJ19.1, RJ19.7, RJ19.10, RJ19.11, RJ19.12, RJ19.14, RJ19.15, RJ19.16, RJ19.21, RJ19.22, RJ19.23, RJ19.24, RJ19.25, RJ19.26, RJ19.31, RJ20.10, RJ20.17, RJ20.23, RR2.2, RR6.2, RR7.2, RR8.2, RR9.2, RR10.2, RR11.2, RR12.2, RTP2.1, RU1.1, RU1.2, RU1.3, RU1.6, RU1.7, RU2.1, RU3.2, RU4.1, RU5.1, RU6.1, RU6.40, RU6.41, RU7.8, RU7.23, RU7.35, RU7.44, RU7.47, RU8.19, RU8.57, RU9.4
Ri2c_chain_0.scl: RJ19.18, RJ20.20, RR4.2, RTP5.1, RU1.13, RU6.10, RU7.21, RU8.37
Ri2c_chain_0.sda: RJ19.19, RJ19.20, RJ20.22, RR5.2, RTP6.1, RU1.14, RU6.9, RU7.22, RU8.36
Rled.res.a: RD2.1, RR6.1
Rled.signal: RD2.2, RU6.33
Rmcu.program_boot_node: RJ16.2, RU6.27
Rmcu.program_en_node: RC15.1, RJ16.6, RR3.2, RU6.3
Rmcu.program_uart_node.a_tx: RJ16.3, RU6.37
Rmcu.program_uart_node.b_tx: RJ16.4, RU6.36
Rmcu_servo.reset_node: RJ17.3, RU6.12, RU7.7
Rmcu_servo.swd.swo: RJ17.6, RU7.42
Rmcu_servo.swd_node.swclk: RJ17.4, RU7.37
Rmcu_servo.swd_node.swdio: RJ17.2, RU7.34
Rmcu_test.gpio.led_0: RD4.2, RU8.4
Rmcu_test.gpio.led_1: RD5.2, RU8.12
Rmcu_test.gpio.led_2: RD6.2, RU8.14
Rmcu_test.gpio.led_3: RD7.2, RU8.16
Rmcu_test.ic.qspi.miso: RU8.55, RU9.2
Rmcu_test.ic.qspi.mosi: RU8.53, RU9.5
Rmcu_test.ic.qspi.sck: RU8.52, RU9.6
Rmcu_test.ic.qspi_cs: RU8.56, RU9.1
Rmcu_test.ic.qspi_sd2: RU8.54, RU9.3
Rmcu_test.ic.qspi_sd3: RU8.51, RU9.7
Rmcu_test.ic.vreg_vout: RC31.1, RC32.1, RC33.1, RU8.23, RU8.45, RU8.50
Rmcu_test.reset_node: RJ18.3, RU8.26
Rmcu_test.swd.swo: RJ18.6, RU8.27
Rmcu_test.swd_node.swclk: RJ18.4, RU8.24
Rmcu_test.swd_node.swdio: RJ18.2, RU8.25
Roled.device.vcomh: RC34.1, RJ19.3, RJ19.29
Roled.device.vp: RC35.1, RJ19.4, RJ19.28
Roled.device.vsl: RJ19.2, RJ19.30, RR13.1
Roled.iref_res.a: RJ19.6, RR12.1
Roled.reset: RJ19.9, RU6.8
Roled.vsl_d1.cathode: RD8.1, RD9.2
Roled.vsl_res.b: RD8.2, RR13.2
Rreg_14v.fb.output: RC5.2, RR1.2, RR2.1, RU3.3
Rreg_14v.inductor.b: RD1.2, RL1.2, RU3.1
Rrgbs.din: RD10.1, RU6.32
Rrgbs.led[0].dout: RD10.3, RD11.1
Rrgbs.led[1].dout: RD11.3, RD12.1
Rrgbs.led[2].dout: RD12.3, RD13.1
Rrgbs.led[3].dout: RD13.3, RD14.1
Rrgbs.led[4].dout: RD14.3, RD15.1
Rrgbs.led[5].dout: RD15.3, RD16.1
Rrgbs.led[6].dout: RD16.3, RD17.1
Rrgbs.led[7].dout: RD17.3, RD18.1
Rrgbs.led[8].dout: RD18.3, RD19.1
Rservo_led.res.a: RD3.1, RR7.1
Rservo_led.signal: RD3.2, RU7.33
Rservos[0].fb: RJ2.4, RU6.38
Rservos[0].pwm: RJ2.1, RU6.34
Rservos[1].fb: RJ3.4, RU6.39
Rservos[1].pwm: RJ3.1, RU6.35
Rservos[2].fb: RJ4.4, RU6.5
Rservos[2].pwm: RJ4.1, RU6.4
Rservos[3].fb: RJ5.4, RU6.7
Rservos[3].pwm: RJ5.1, RU6.6
Rservos[4].fb: RJ6.4, RU7.10
Rservos[4].pwm: RJ6.1, RU7.41
Rservos[5].fb: RJ7.4, RU7.11
Rservos[5].pwm: RJ7.1, RU7.43
Rservos[6].fb: RJ8.4, RU7.12
Rservos[6].pwm: RJ8.1, RU7.45
Rservos[7].fb: RJ9.4, RU7.14
Rservos[7].pwm: RJ9.1, RU7.26
Rservos[8].fb: RJ10.4, RU7.19
Rservos[8].pwm: RJ10.1, RU7.32
Rservos[9].fb: RJ11.4, RU7.18
Rservos[9].pwm: RJ11.1, RU7.31
Rservos[10].fb: RJ12.4, RU7.17
Rservos[10].pwm: RJ12.1, RU7.30
Rservos[11].fb: RJ13.4, RU7.15
Rservos[11].pwm: RJ13.1, RU7.28
Rservos_cam[0].fb: RJ14.4, RU7.13
Rservos_cam[0].pwm: RJ14.1, RU7.46
Rservos_cam[1].fb: RJ15.4, RU7.16
Rservos_cam[1].pwm: RJ15.1, RU7.29
Rtest_led.led[0].res.a: RD4.1, RR8.1
Rtest_led.led[1].res.a: RD5.1, RR9.1
Rtest_led.led[2].res.a: RD6.1, RR10.1
Rtest_led.led[3].res.a: RD7.1, RR11.1
Rv1v2: RC12.1, RJ20.15, RU5.2
Rv2v5: RC10.1, RJ20.21, RU4.2
Rv3v3: RC1.1, RC2.1, RC4.1, RC13.1, RC14.1, RC16.1, RC17.1, RC18.1, RC19.1, RC20.1, RC21.1, RC22.1, RC23.1, RC24.1, RC25.1, RC26.1, RC27.1, RC28.1, RC29.1, RC30.1, RC36.1, RC38.1, RJ16.1, RJ17.1, RJ18.1, RJ19.8, RJ19.13, RJ19.17, RJ20.14, RR3.1, RR4.1, RR5.1, RR14.1, RTP3.1, RU1.5, RU1.8, RU1.12, RU2.3, RU6.2, RU7.1, RU7.9, RU7.24, RU7.36, RU7.48, RU8.1, RU8.10, RU8.22, RU8.33, RU8.42, RU8.43, RU8.44, RU8.48, RU8.49, RU9.8
Rv14: RC5.1, RC7.1, RC8.1, RC37.1, RD1.1, RJ19.5, RJ19.27, RR1.1, RTP4.1
Rvbatt: RC3.1, RC6.1, RC9.1, RC11.1, RD10.2, RD11.2, RD12.2, RD13.2, RD14.2, RD15.2, RD16.2, RD17.2, RD18.2, RD19.2, RJ1.2, RJ2.2, RJ3.2, RJ4.2, RJ5.2, RJ6.2, RJ7.2, RJ8.2, RJ9.2, RJ10.2, RJ11.2, RJ12.2, RJ13.2, RJ14.2, RJ15.2, RL1.1, RTP1.1, RU2.2, RU3.4, RU3.5, RU4.3, RU5.3
